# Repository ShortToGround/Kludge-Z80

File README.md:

# Kludge-Z80

A custom and completely kludged together Z80 project.

Table of Contents:
- [Kludge-Z80](#kludge-z80)
  - [About](#about)
  - [Backplane](#backplane)
  - [Card List](#card-list)
    - [Compact Flash Card](#compact-flash-card)
    - [IDE Card](#ide-card)
    - [CPU Card](#cpu-card)
    - [Memory/RAM Card](#memoryram-card)
    - [Network Card](#network-card)
    - [Protoboard Card](#protoboard-card)
    - [PS/2 Card](#ps2-card)
    - [Real-time Clock Card](#real-time-clock-card)
    - [Serial Card](#serial-card)
    - [Sound Card](#sound-card)
    - [Video Card](#video-card)
  - [Bill of Materials](#bill-of-materials)

## About
I've been working on this project off and on since 2017 or, though it was mostly off until recently!
I've designed all of the hardware from scratch, though I'm totally new to this and have no idea what I'm doing.
That's why the project is called Kludge :)

## Backplane
The backplane is a 12-slot board with a full breakout of the Z80 bus. It also has a few spare pins on the bus for future use as well.

I wanted this backplane to be "motherboard-like". At first I was even going to put the CPU and ROM directly on the board! But to make it "motherboard-like" I designed it with status lights (with a breakout too in case I ever put this in a case and want case lights), the reset button on-board, and address decoding on-board as well.

I have designed it to support 5V at 2A load (actually has 3A rated power components!) with a big chunky sliding power switch. This should allow the use of hard disks in the future if they are 5V-only.

NOTE: Because my backplane board length is so long AND the system clock is supplied on the bus directly, I worry about signal reflections. So the backplane features an active termination on-board that holds all of the signals at 2.7V in a push-pull arrangement. 

## Card List
### Compact Flash Card
Compact flash actually has an 8-bit mode built into the spec, which makes interfacing it with vintage 8-bit CPUs pretty easy.

However, in the case of the Z80 the I/O timing differences between the CF and Z80 CPU don't line up perfectly. If you don't account for this in your design you will encounter a decent amount of compact flash cards that will refuse to work, especially newer and faster cards.

The solution is to properly delay the Z80 timings to fit the compact flash true IDE spec.

Someone a lot smarter than me named Tadeusz Pycio came up with a delay circuit to fix this issue.

You can find his blog about it [here](http://www.vtsys.pl/interface-compact-flash/). If you want to read it in English you will need to enter it into google translate though. Google Translate does an excellent job though and its very understandable!

After implementing his circuit into my design I haven't came across a single compact flash card that wouldn't work.

### IDE Card
This is basically the compact flash card circuit but with an 40-pin IDE port instead of compact flash port.

### CPU Card
This is just simply the Z80 CPU broken out onto the bus. There are some pull-ups for the various control signals. It is running off of a 10 MHz oscillator.

I originally designed the RTC circuit to be included but it took up almost all the space on the board and over crowded the CPU and wasn't aesthetically pleasing.

### Memory/RAM Card
This card holds the RAM and EEPROM chips. RAM is bank switched using I/O and also includes the option to totally deactivate the ROM after boot (useful if you are loading a binary on boot from elsewhere).

I adapted some of John's banking and shadow select circuitry into my own.
His documentation and videos have been incredibly useful.

You can visit his awesome Z80 Retro! project [here](https://github.com/Z80-Retro/2063-Z80).

### Network Card
This really should be called "Fast SPI Card" because it's just a parallel
to SPI interface with a header. This circuit was very tricky to build and
I referenced a LOT of other similar builds to piece it together.

### Protoboard Card
A card used to prototype circuits with the Kludge bus.

It's just a 38 x 32 array of 2.54mm spaced pin holes for prototyping.

Why 38 x 32? Because its as much as I could fit in a 100mm x 100mm board to save fab costs :D

### PS/2 Card
This card granted support for both a mouse and keyboard.
It uses a HT6542B to handle all of the PS/2 communication and timing.

### Real-time Clock Card
Like the network card, this is just an SPI circuit as well but the 
RTC IC is embedded on board and this runs a LOT slower than the network card circuit does.

### Serial Card
This card has a single 16550DN UART on-board for serial communication.

### Sound Card
This is a sound card built around the class AY-3-8910.

I am looking to add a second chip in V2 for 3 channel stereo output.

### Video Card
This is centered around an Upduino v3.1 to drive a VGA display. 
The Upduino uses a Lattice iCE40 UP5K UG48 FPGA.
The verilog code for this is available in its own dedicated repo.

## Bill of Materials
The list is pretty large for this whole project. I will compile it and update this later.

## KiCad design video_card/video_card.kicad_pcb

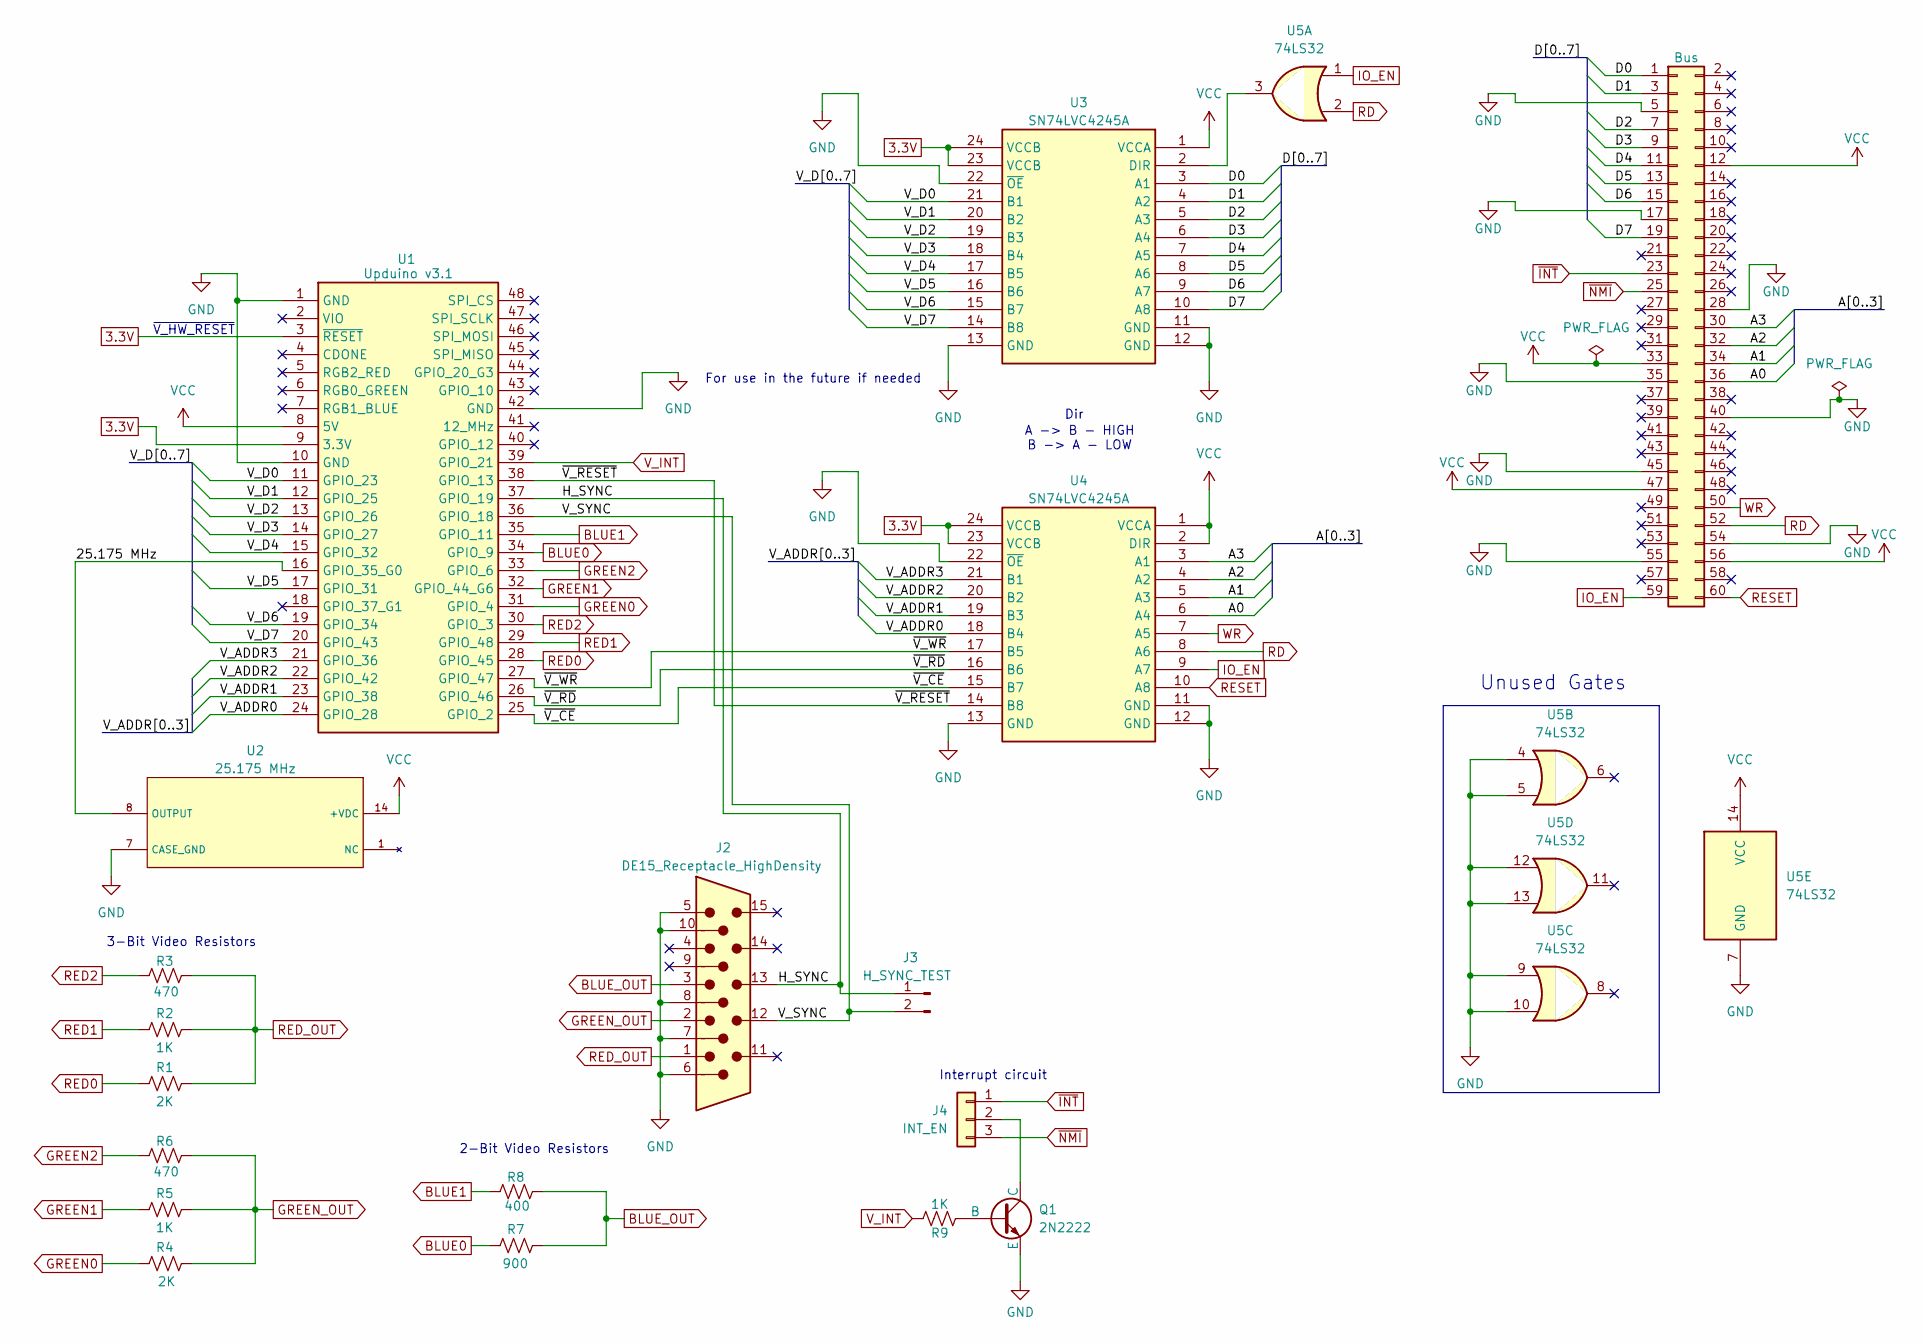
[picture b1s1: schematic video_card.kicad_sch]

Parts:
J1: Bus; PinHeader_2x30_P2.54mm_Vertical
J2: DE15_Receptacle_HighDensity; AMPHENOL_ICD15S13E4GX00LF
J3: H_SYNC_TEST; PinHeader_1x02_P2.54mm_Vertical
J4: INT_EN; PinHeader_1x03_P2.54mm_Vertical
Q1: 2N2222; TO-92
R1, R4: 2K; R_Axial_DIN0207_L6.3mm_D2.5mm_P10.16mm_Horizontal
R2, R5, R9: 1K; R_Axial_DIN0207_L6.3mm_D2.5mm_P10.16mm_Horizontal
R3, R6: 470; R_Axial_DIN0207_L6.3mm_D2.5mm_P10.16mm_Horizontal
R7: 900; R_Axial_DIN0207_L6.3mm_D2.5mm_P10.16mm_Horizontal
R8: 400; R_Axial_DIN0207_L6.3mm_D2.5mm_P10.16mm_Horizontal
U1: Upduino v3.1; UPDUINO V3.1
U2: 25.175 MHz; OSC_ECS-100AX-018
U3, U4: SN74LVC4245A; SN74LVC4245ADWR
U5: 74LS32; DIP-14_W7.62mm_Socket

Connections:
3.3V: U1.3 (~RESET), U1.9 (3.3V), U3.23 (VCCB), U3.24 (VCCB), U4.23 (VCCB), U4.24 (VCCB)
/25.175 MHz: U1.16 (GPIO_35_G0), U2.8 (OUTPUT)
/A0: J1.36, U4.6 (A4)
/A1: J1.34, U4.5 (A3)
/A2: J1.32, U4.4 (A2)
/A3: J1.30, U4.3 (A1)
/D0: J1.1, U3.3 (A1)
/D1: J1.3, U3.4 (A2)
/D2: J1.7, U3.5 (A3)
/D3: J1.9, U3.6 (A4)
/D4: J1.11, U3.7 (A5)
/D5: J1.13, U3.8 (A6)
/D6: J1.15, U3.9 (A7)
/D7: J1.19, U3.10 (A8)
/H_SYNC: J2.13, J3.1, U1.37 (GPIO_19)
/V_ADDR0: U1.24 (GPIO_28), U4.18 (B4)
/V_ADDR1: U1.23 (GPIO_38), U4.19 (B3)
/V_ADDR2: U1.22 (GPIO_42), U4.20 (B2)
/V_ADDR3: U1.21 (GPIO_36), U4.21 (B1)
/V_D0: U1.11 (GPIO_23), U3.21 (B1)
/V_D1: U1.12 (GPIO_25), U3.20 (B2)
/V_D2: U1.13 (GPIO_26), U3.19 (B3)
/V_D3: U1.14 (GPIO_27), U3.18 (B4)
/V_D4: U1.15 (GPIO_32), U3.17 (B5)
/V_D5: U1.17 (GPIO_31), U3.16 (B6)
/V_D6: U1.19 (GPIO_34), U3.15 (B7)
/V_D7: U1.20 (GPIO_43), U3.14 (B8)
/V_SYNC: J2.12, J3.2, U1.36 (GPIO_18)
/~V_CE: U1.25 (GPIO_2), U4.15 (B7)
/~V_RD: U1.26 (GPIO_46), U4.16 (B6)
/~V_RESET: U1.38 (GPIO_13), U4.14 (B8)
/~V_WR: U1.27 (GPIO_47), U4.17 (B5)
BLUE0: R7.1, U1.34 (GPIO_9)
BLUE1: R8.1, U1.35 (GPIO_11)
BLUE_OUT: J2.3, R7.2, R8.2
GND: J1.5, J1.17, J1.28, J1.35, J1.40, J1.45, J1.54, J1.55, J2.5, J2.6, J2.7, J2.8, J2.10, Q1.3 (E), U1.1 (GND), U1.10 (GND), U1.42 (GND), U2.7 (CASE_GND), U3.11 (GND), U3.12 (GND), U3.13 (GND), U3.22 (~OE), U4.11 (GND), U4.12 (GND), U4.13 (GND), U4.22 (~OE), U5.4, U5.5, U5.7 (GND), U5.9, U5.10, U5.12, U5.13
GREEN0: R4.1, U1.31 (GPIO_4)
GREEN1: R5.1, U1.32 (GPIO_44_G6)
GREEN2: R6.1, U1.33 (GPIO_6)
GREEN_OUT: J2.2, R4.2, R5.2, R6.2
IO_EN: J1.59, U4.9 (A7), U5.1
unnamed: J4.2, Q1.1 (C)
unnamed: Q1.2 (B), R9.1
unnamed: U3.2 (DIR), U5.3
RD: J1.52, U4.8 (A6), U5.2
RED0: R1.1, U1.28 (GPIO_45)
RED1: R2.1, U1.29 (GPIO_48)
RED2: R3.1, U1.30 (GPIO_3)
RED_OUT: J2.1, R1.2, R2.2, R3.2
RESET: J1.60, U4.10 (A8)
VCC: J1.12, J1.33, J1.47, J1.56, U1.8 (5V), U2.14 (+VDC), U3.1 (VCCA), U4.1 (VCCA), U4.2 (DIR), U5.14 (VCC)
V_INT: R9.2, U1.39 (GPIO_21)
WR: J1.50, U4.7 (A5)
~INT: J1.23, J4.1
~NMI: J1.25, J4.3

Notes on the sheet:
Unused Gates
A -> B - HIGH B -> A - LOW
Dir
2-Bit Video Resistors
~{V_HW_RESET}
Interrupt circuit
3-Bit Video Resistors
For use in the future if needed

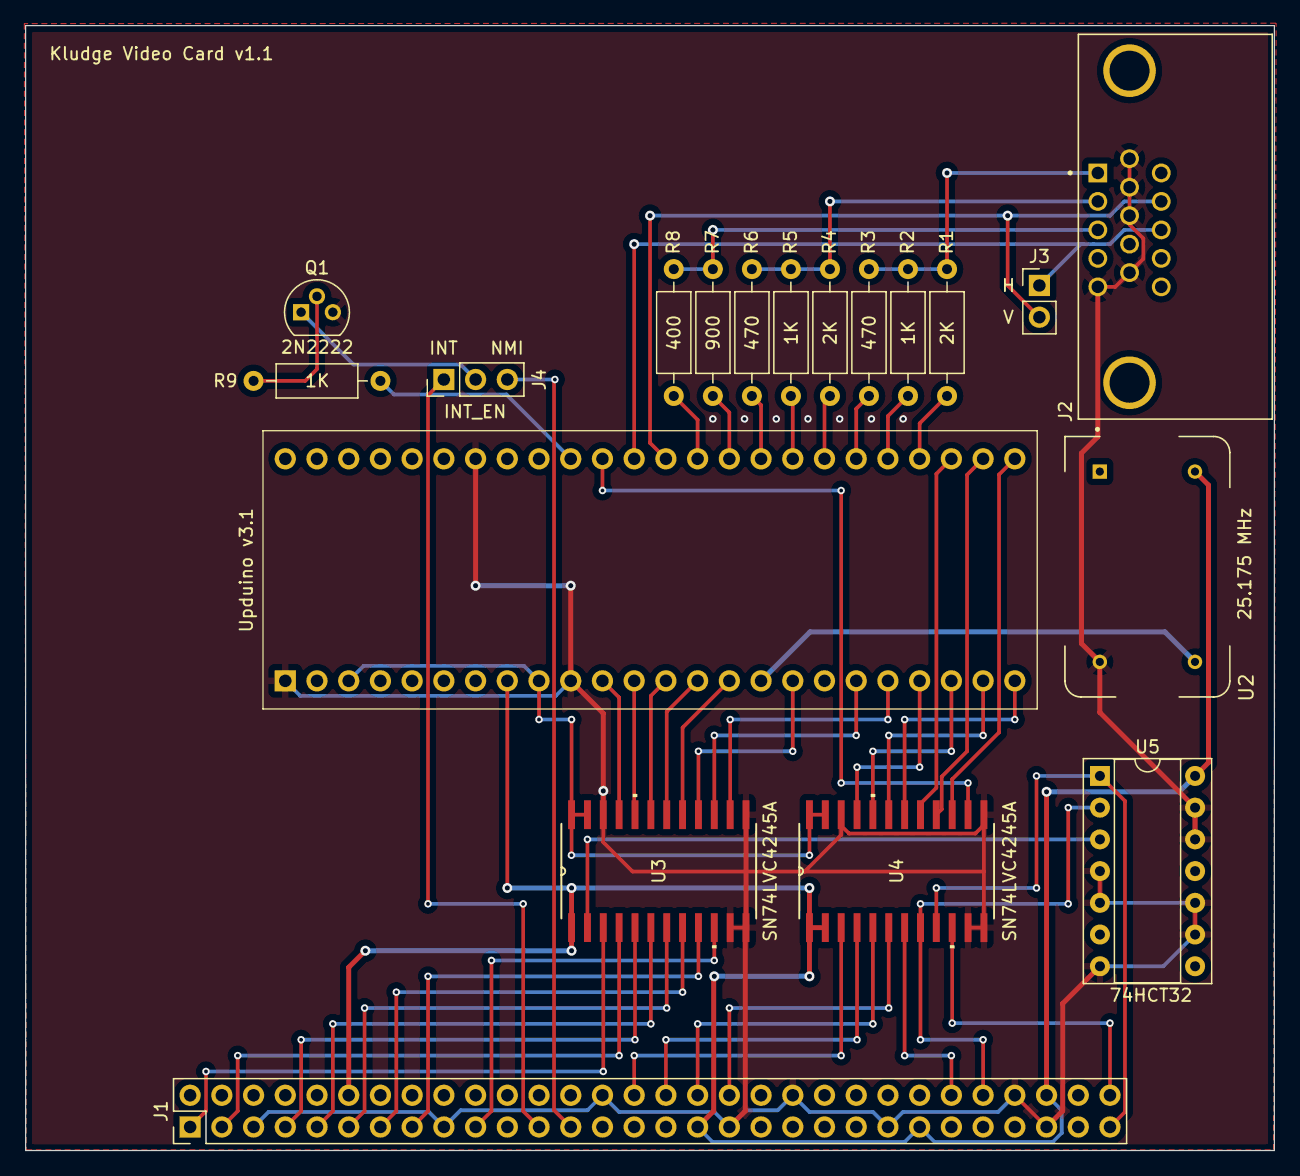
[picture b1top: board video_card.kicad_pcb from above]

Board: 2 copper layers, 100.0 x 90.1 mm, 19 parts (0 on the bottom side), 55 nets.

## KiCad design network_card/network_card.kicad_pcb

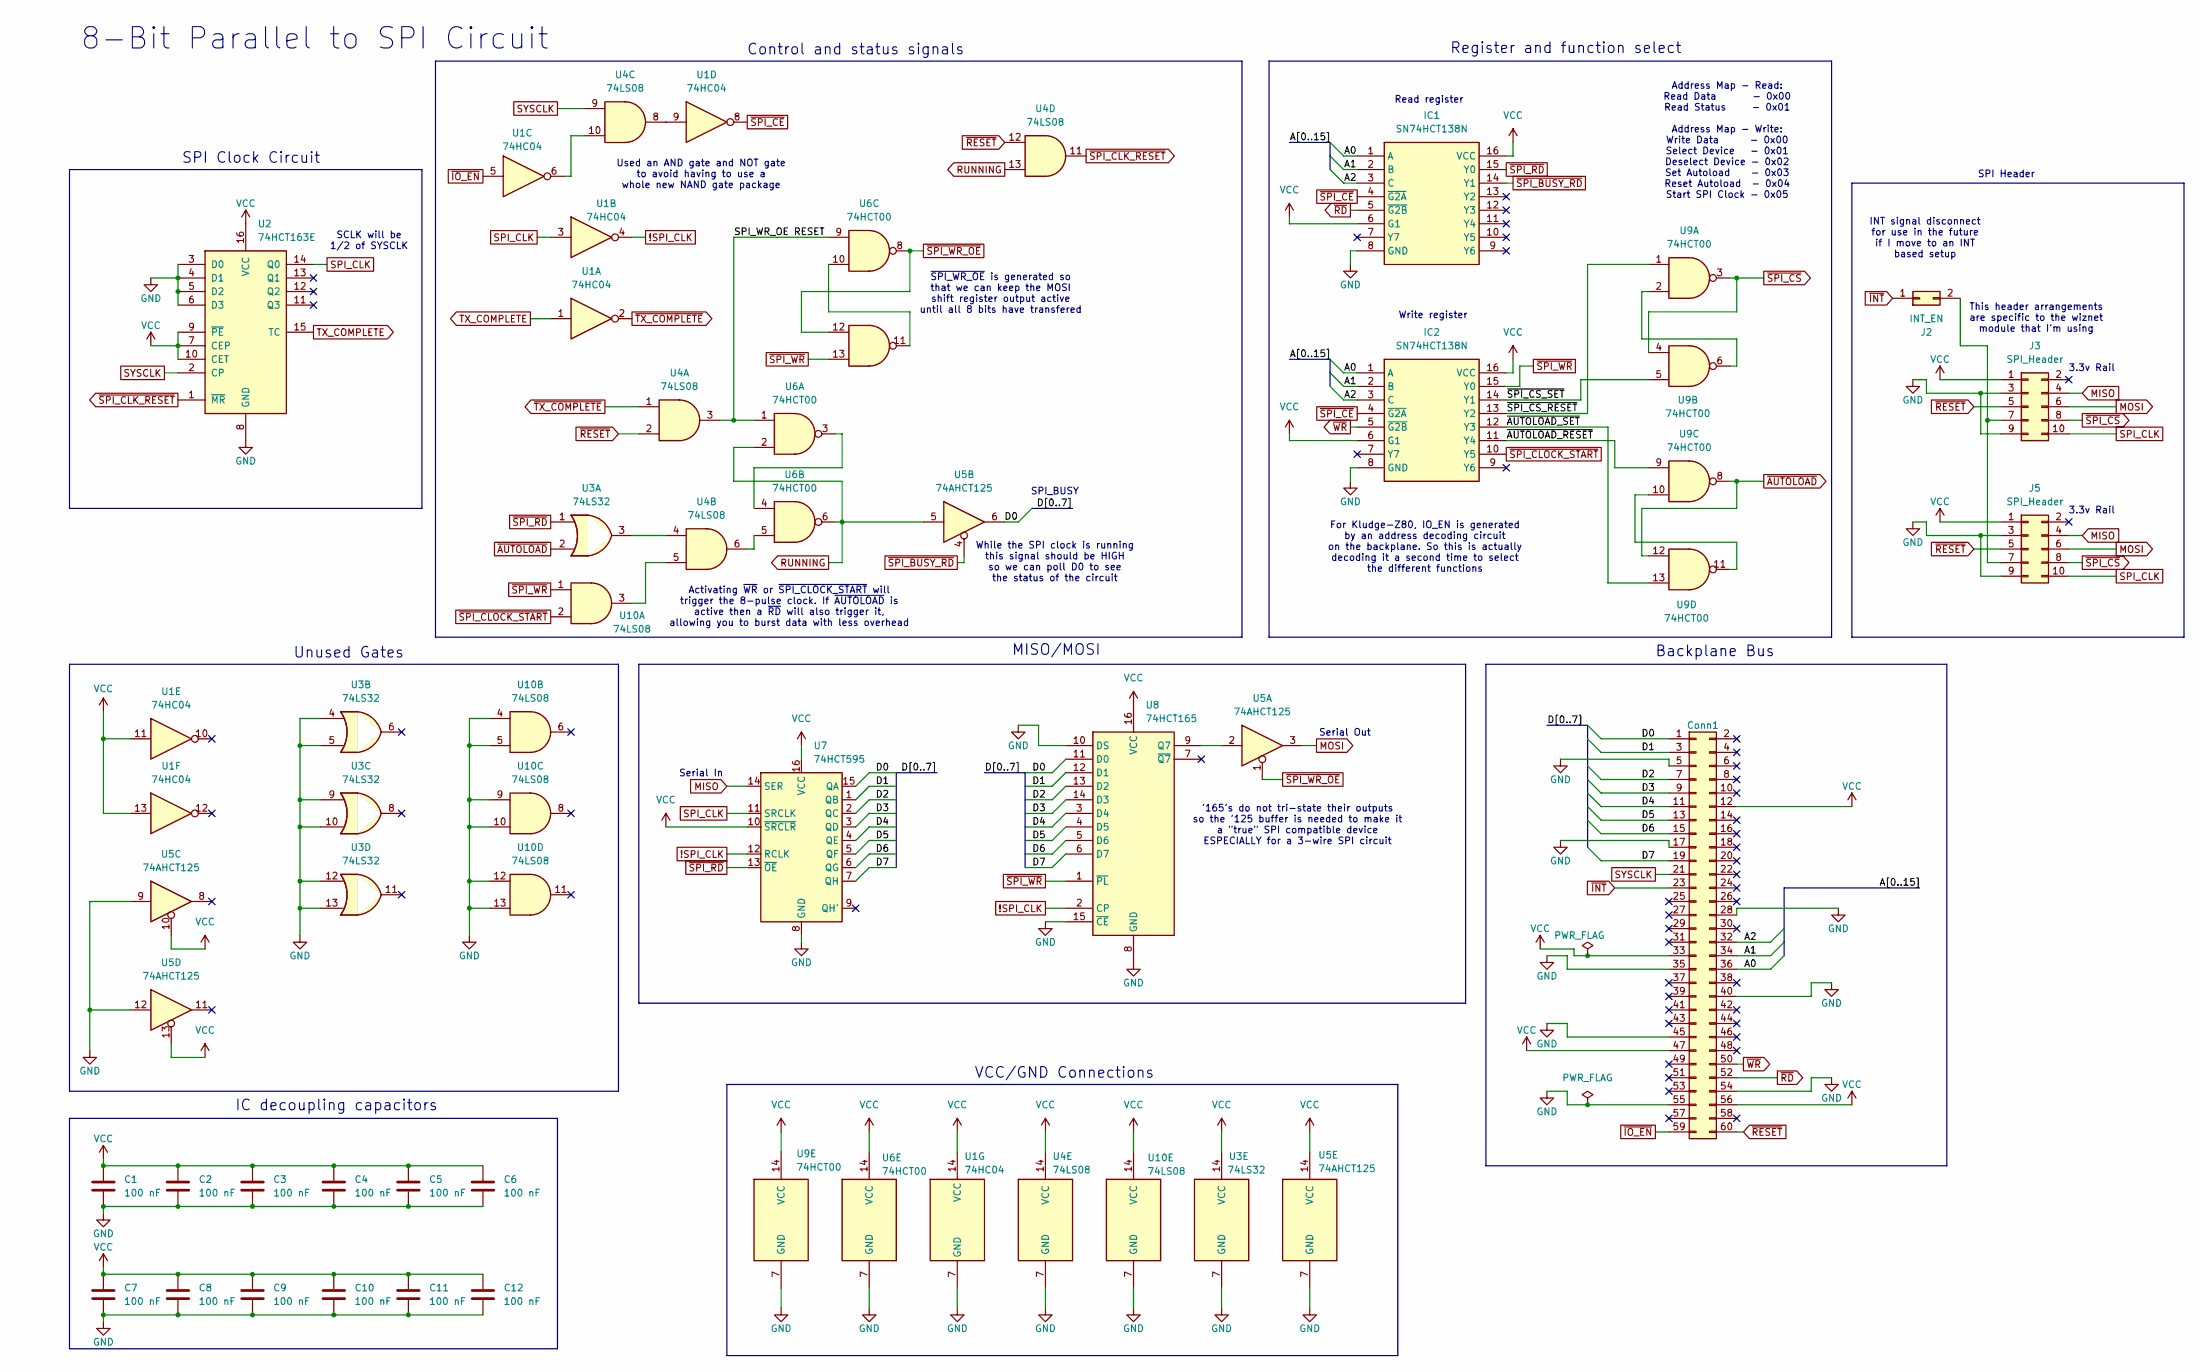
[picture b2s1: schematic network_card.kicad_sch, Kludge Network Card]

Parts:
C1, C2, C3, C4, C5, C6, C7, C8, C9, C10, C11, C12: 100 nF; C_Disc_D3.0mm_W1.6mm_P2.50mm
IC1, IC2: SN74HCT138N; DIP-16_W7.62mm_Socket; Mouser Part Number 595-SN74HCT138N
J1: Conn1; PinHeader_2x30_P2.54mm_Vertical
J2: INT_EN; PinHeader_2x01_P2.54mm_Vertical
J3: SPI_Header; PinHeader_2x05_P2.54mm_Vertical
J5: SPI_Header; IDC-Header_2x05_P2.54mm_Vertical
U1: 74HC04; DIP-14_W7.62mm_Socket
U2: 74HCT163E; DIP-16_W7.62mm_Socket
U3: 74LS32; DIP-14_W7.62mm_Socket
U4, U10: 74LS08; DIP-14_W7.62mm_Socket
U5: 74AHCT125; DIP-14_W7.62mm_Socket
U6, U9: 74HCT00; DIP-14_W7.62mm_Socket
U7: 74HCT595; DIP-16_W7.62mm_Socket
U8: 74HCT165; DIP-16_W7.62mm_Socket

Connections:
!SPI_CLK: U1.4, U7.12 (RCLK), U8.2 (CP)
/A0: IC1.1 (A), IC2.1 (A), J1.36
/A1: IC1.2 (B), IC2.2 (B), J1.34
/A2: IC1.3 (C), IC2.3 (C), J1.32
/D0: J1.1, U5.6, U7.15 (QA), U8.11 (D0)
/D1: J1.3, U7.1 (QB), U8.12 (D1)
/D2: J1.7, U7.2 (QC), U8.13 (D2)
/D3: J1.9, U7.3 (QD), U8.14 (D3)
/D4: J1.11, U7.4 (QE), U8.3 (D4)
/D5: J1.13, U7.5 (QF), U8.4 (D5)
/D6: J1.15, U7.6 (QG), U8.5 (D6)
/D7: J1.19, U7.7 (QH), U8.6 (D7)
/SPI_WR_OE RESET: U4.3, U6.1, U6.9
/~AUTOLOAD_RESET: IC2.11 (Y4), U9.9
/~AUTOLOAD_SET: IC2.12 (Y3), U9.13
/~SPI_CS_RESET: IC2.13 (Y2), U9.1
/~SPI_CS_SET: IC2.14 (Y1), U9.5
GND: C1.2, C2.2, C3.2, C4.2, C5.2, C6.2, C7.2, C8.2, C9.2, C10.2, C11.2, C12.2, IC1.8 (GND), IC2.8 (GND), J1.5, J1.17, J1.28, J1.35, J1.40, J1.45, J1.54, J1.55, J3.3, J3.9, J5.3, J5.9, U1.7 (GND), U2.3 (D0), U2.4 (D1), U2.5 (D2), U2.6 (D3), U2.8 (GND), U3.4, U3.5, U3.7 (GND), U3.9, U3.10, U3.12, U3.13, U4.7 (GND), U5.7 (GND), U5.9, U5.12, U6.7 (GND), U7.8 (GND), U8.8 (GND), U8.10 (DS), U8.15 (~CE), U9.7 (GND), U10.4, U10.5, U10.7 (GND), U10.9, U10.10, U10.12, U10.13
MISO: J3.4, J5.4, U7.14 (SER)
MOSI: J3.6, J5.6, U5.3
unnamed: J2.2, J3.7, J5.7
unnamed: U1.6, U4.10
unnamed: U1.9, U4.8
unnamed: U3.3, U4.4
unnamed: U4.6, U6.5
unnamed: U6.3, U6.4
unnamed: U6.10, U6.11
unnamed: U5.2, U8.9 (Q7)
unnamed: U9.2, U9.6
unnamed: U9.10, U9.11
unnamed: U4.5, U10.3
RUNNING: U4.13, U5.5, U6.2, U6.6
SPI_CLK: J3.10, J5.10, U1.3, U2.14 (Q0), U7.11 (SRCLK)
SYSCLK: J1.21, U2.2 (CP), U4.9
TX_COMPLETE: U1.1, U2.15 (TC)
VCC: C1.1, C2.1, C3.1, C4.1, C5.1, C6.1, C7.1, C8.1, C9.1, C10.1, C11.1, C12.1, IC1.6 (G1), IC1.16 (VCC), IC2.6 (G1), IC2.16 (VCC), J1.12, J1.33, J1.47, J1.56, J3.1, J5.1, U1.11, U1.13, U1.14 (VCC), U2.7 (CEP), U2.9 (~PE), U2.10 (CET), U2.16 (VCC), U3.14 (VCC), U4.14 (VCC), U5.10, U5.13, U5.14 (VCC), U6.14 (VCC), U7.10 (~SRCLR), U7.16 (VCC), U8.16 (VCC), U9.14 (VCC), U10.14 (VCC)
~AUTOLOAD: U3.2, U9.8, U9.12
~INT: J1.23, J2.1
~IO_EN: J1.59, U1.5
~RD: IC1.5 (~G2B), J1.52
~RESET: J1.60, J3.5, J5.5, U4.2, U4.12
~SPI_BUSY_RD: IC1.14 (Y1), U5.4
~SPI_CE: IC1.4 (~G2A), IC2.4 (~G2A), U1.8
~SPI_CLK_RESET: U2.1 (~MR), U4.11
~SPI_CLOCK_START: IC2.10 (Y5), U10.2
~SPI_CS: J3.8, J5.8, U9.3, U9.4
~SPI_RD: IC1.15 (Y0), U3.1, U7.13 (~OE)
~SPI_WR_OE: U5.1, U6.8, U6.12
~SPI_WR: IC2.15 (Y0), U6.13, U8.1 (~PL), U10.1
~TX_COMPLETE: U1.2, U4.1
~WR: IC2.5 (~G2B), J1.50

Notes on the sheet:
Used an AND gate and NOT gate to avoid having to use a whole new NAND gate package
MISO/MOSI
This header arrangements are specific to the wiznet module that I'm using
Control and status signals
Write register
3.3v Rail
Serial In
Serial Out
While the SPI clock is running this signal should be HIGH so we can poll D0 to see the status of the circuit
Address Map - Read: Read Data - 0x00 Read Status - 0x01 Address Map - Write: Write Data - 0x00 Select Device - 0x01 Deselect Device - 0x02 Set Autoload - 0x03 Reset Autoload - 0x04 Start SPI Clock - 0x05
SPI Header
IC decoupling capacitors
Unused Gates
For Kludge-Z80, IO_EN is generated by an address decoding circuit on the backplane. So this is actually decoding it a second time to select the different functions
Activating ~{WR} or ~{SPI_CLOCK_START} will trigger the 8-pulse clock. If ~{AUTOLOAD} is active then a ~{RD} will also trigger it, allowing you to burst data with less overhead
8-Bit Parallel to SPI Circuit
Register and function select
~{SPI_WR_OE} is generated so that we can keep the MOSI shift register output active until all 8 bits have transfered
Backplane Bus
VCC/GND Connections
SCLK will be 1/2 of SYSCLK
SPI_BUSY
Read register
INT signal disconnect for use in the future if I move to an INT based setup
SPI Clock Circuit
'165's do not tri-state their outputs so the '125 buffer is needed to make it a "true" SPI compatible device ESPECIALLY for a 3-wire SPI circuit

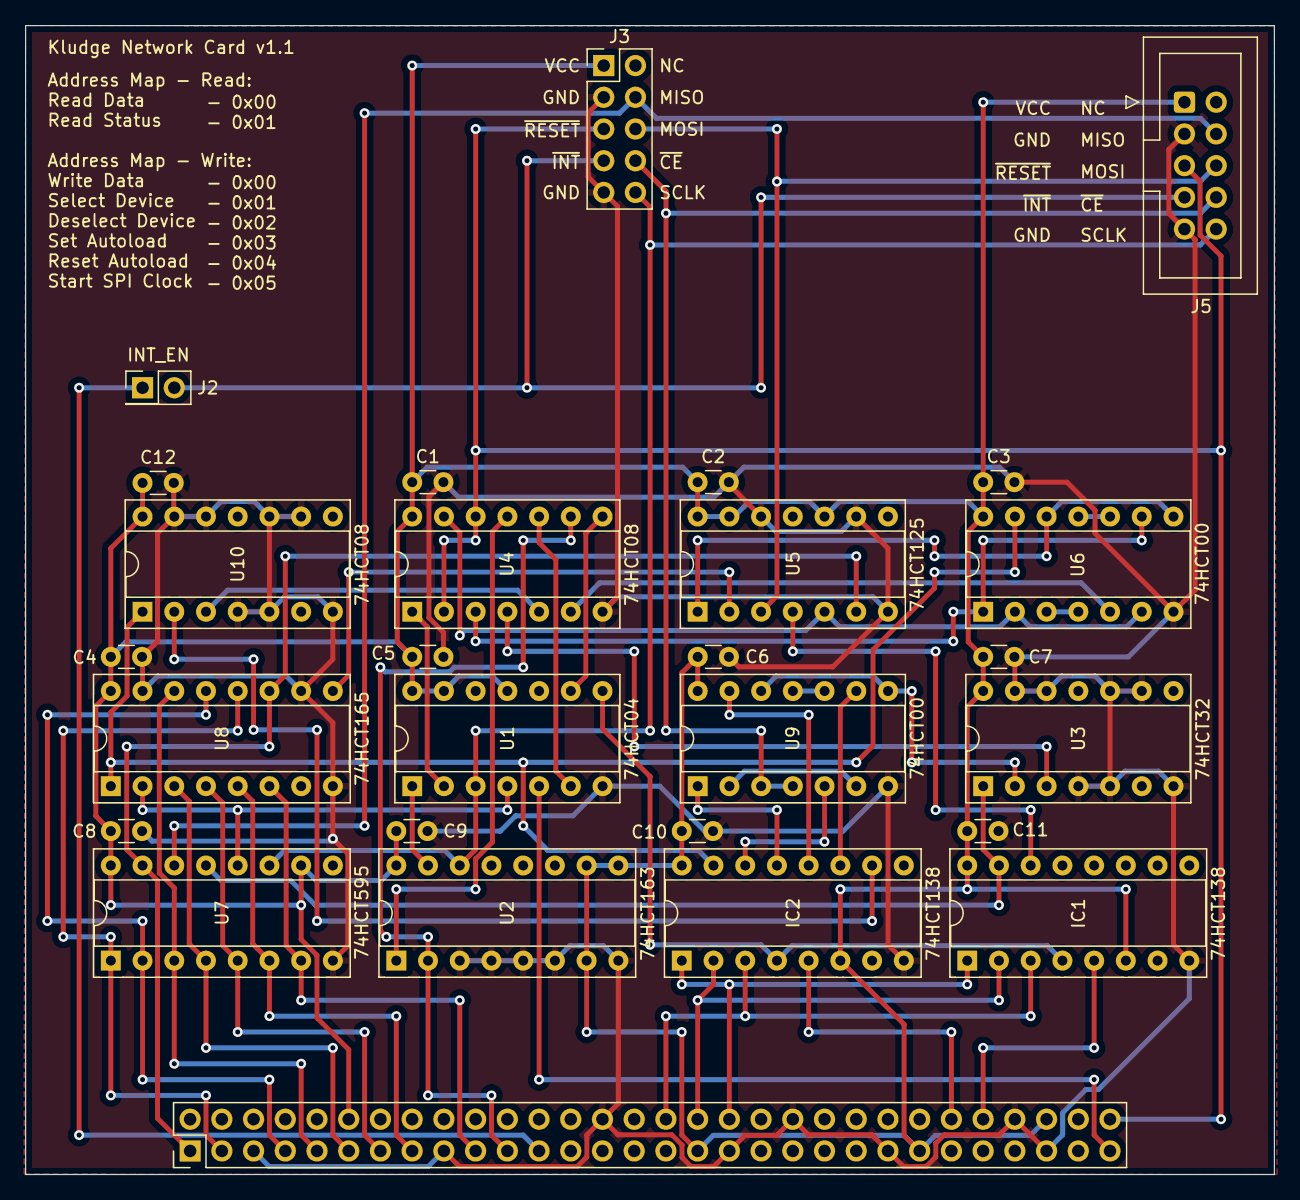
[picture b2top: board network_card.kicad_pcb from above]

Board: 2 copper layers, 100.0 x 92.0 mm, 28 parts (0 on the bottom side), 51 nets.

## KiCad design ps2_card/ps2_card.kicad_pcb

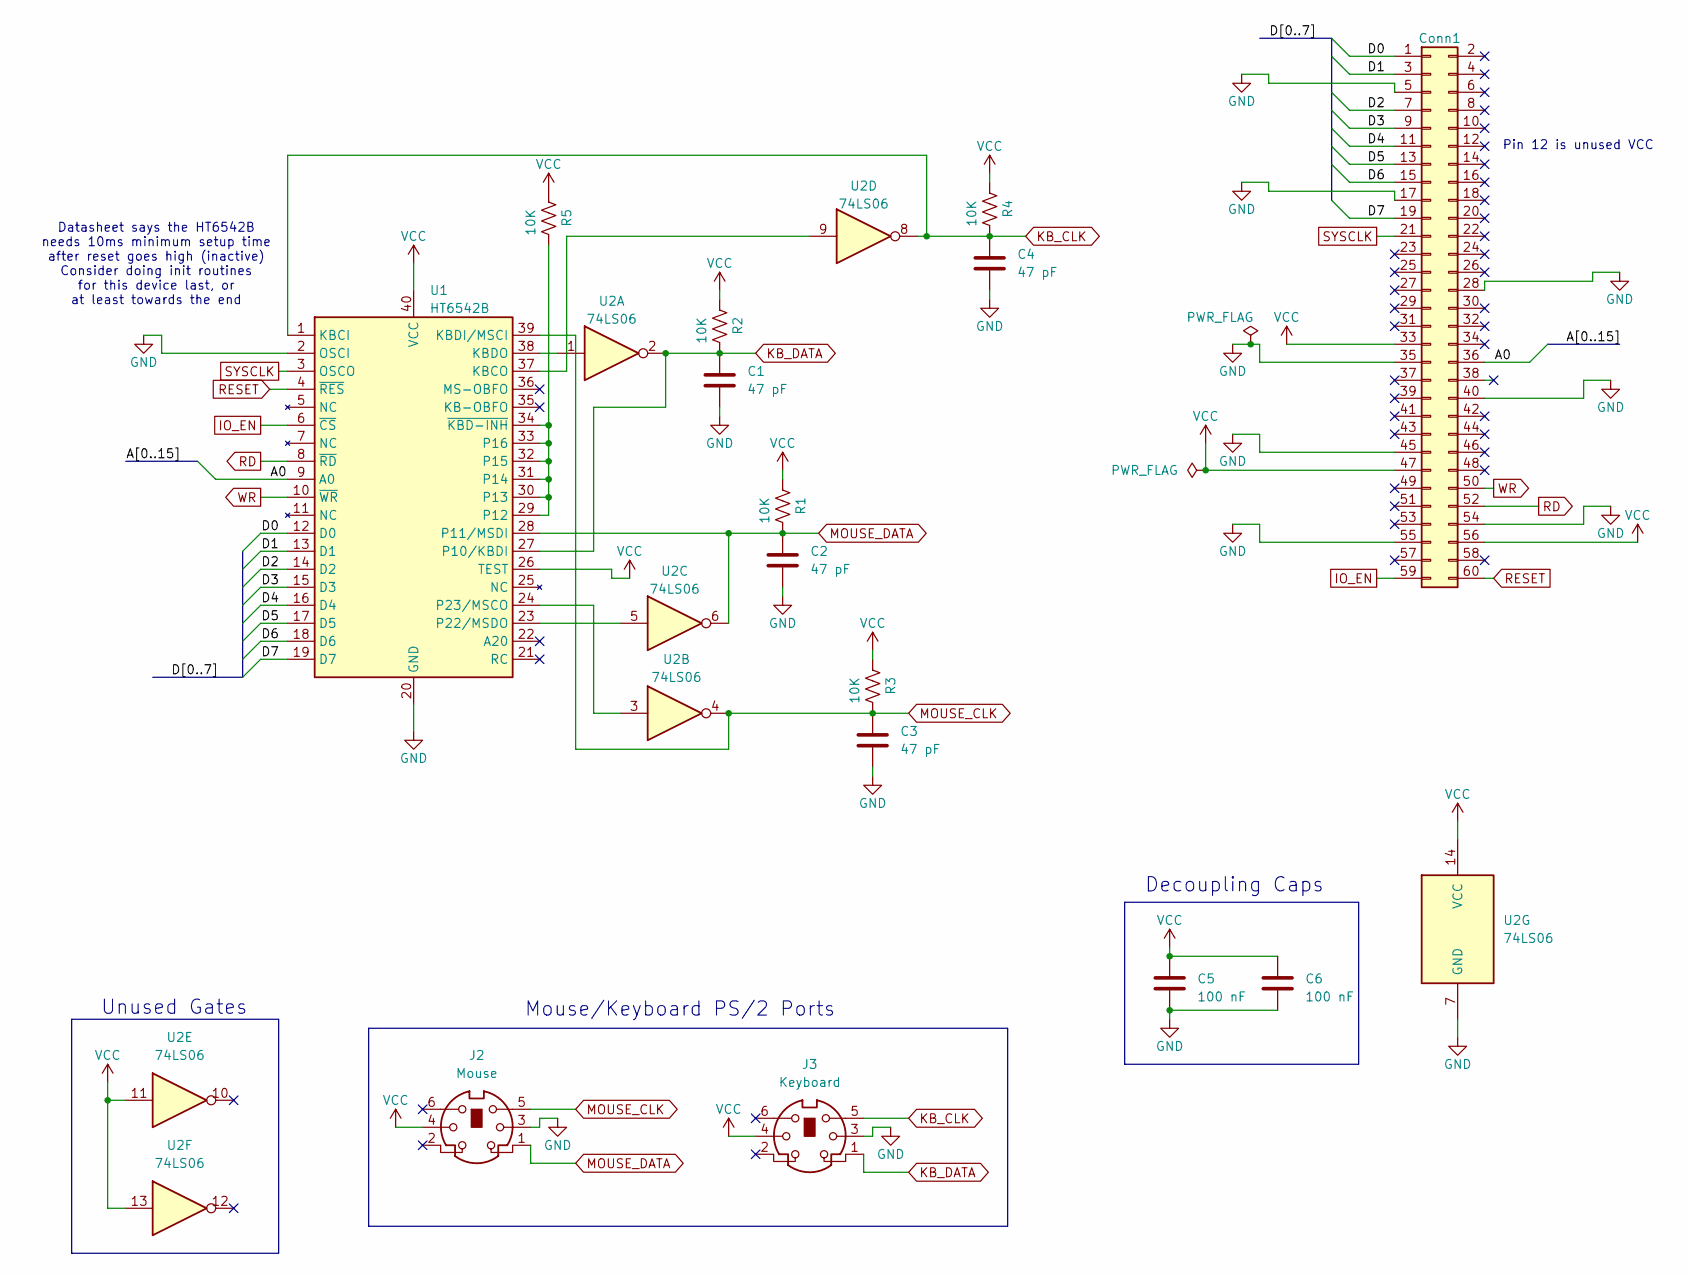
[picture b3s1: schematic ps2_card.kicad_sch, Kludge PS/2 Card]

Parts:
C1, C2, C3, C4: 47 pF; C_Disc_D3.0mm_W1.6mm_P2.50mm
C5, C6: 100 nF; C_Disc_D3.0mm_W1.6mm_P2.50mm
J1: Conn1; PinHeader_2x30_P2.54mm_Vertical
J2: Mouse; CONN_5749180-1_TYC
J3: Keyboard; CONN_5749180-1_TYC
R1, R2, R3, R4, R5: 10K; R_Axial_DIN0207_L6.3mm_D2.5mm_P10.16mm_Horizontal
U1: HT6542B; DIP-40_W15.24mm
U2: 74LS06; DIP-14_W7.62mm

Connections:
/A0: J1.36, U1.9 (A0)
/D0: J1.1, U1.12 (D0)
/D1: J1.3, U1.13 (D1)
/D2: J1.7, U1.14 (D2)
/D3: J1.9, U1.15 (D3)
/D4: J1.11, U1.16 (D4)
/D5: J1.13, U1.17 (D5)
/D6: J1.15, U1.18 (D6)
/D7: J1.19, U1.19 (D7)
GND: C1.2, C2.2, C3.2, C4.2, C5.2, C6.2, J1.5, J1.17, J1.28, J1.35, J1.40, J1.45, J1.54, J1.55, J2.3, J3.3, U1.2 (OSCI), U1.20 (GND), U2.7 (GND)
IO_EN: J1.59, U1.6 (~CS)
KB_CLK: C4.1, J3.5, R4.2, U1.1 (KBCI), U2.8
KB_DATA: C1.1, J3.1, R2.2, U1.27 (P10/KBDI), U2.2
MOUSE_CLK: C3.1, J2.5, R3.2, U1.39 (KBDI/MSCI), U2.4
MOUSE_DATA: C2.1, J2.1, R1.2, U1.28 (P11/MSDI), U2.6
unnamed: U1.37 (KBCO), U2.9
unnamed: U1.38 (KBDO), U2.1
unnamed: R5.2, U1.29 (P12), U1.30 (P13), U1.31 (P14), U1.32 (P15), U1.33 (P16), U1.34 (~KBD-INH)
unnamed: U1.23 (P22/MSDO), U2.5
unnamed: U1.24 (P23/MSCO), U2.3
RD: J1.52, U1.8 (~RD)
RESET: J1.60, U1.4 (~RES)
SYSCLK: J1.21, U1.3 (OSCO)
VCC: C5.1, C6.1, J1.33, J1.47, J1.56, J2.4, J3.4, R1.1, R2.1, R3.1, R4.1, R5.1, U1.26 (TEST), U1.40 (VCC), U2.11, U2.13, U2.14 (VCC)
WR: J1.50, U1.10 (~WR)

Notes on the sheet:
Datasheet says the HT6542B needs 10ms minimum setup time after reset goes high (inactive) Consider doing init routines for this device last, or at least towards the end
Unused Gates
Pin 12 is unused VCC
Mouse/Keyboard PS/2 Ports
Decoupling Caps

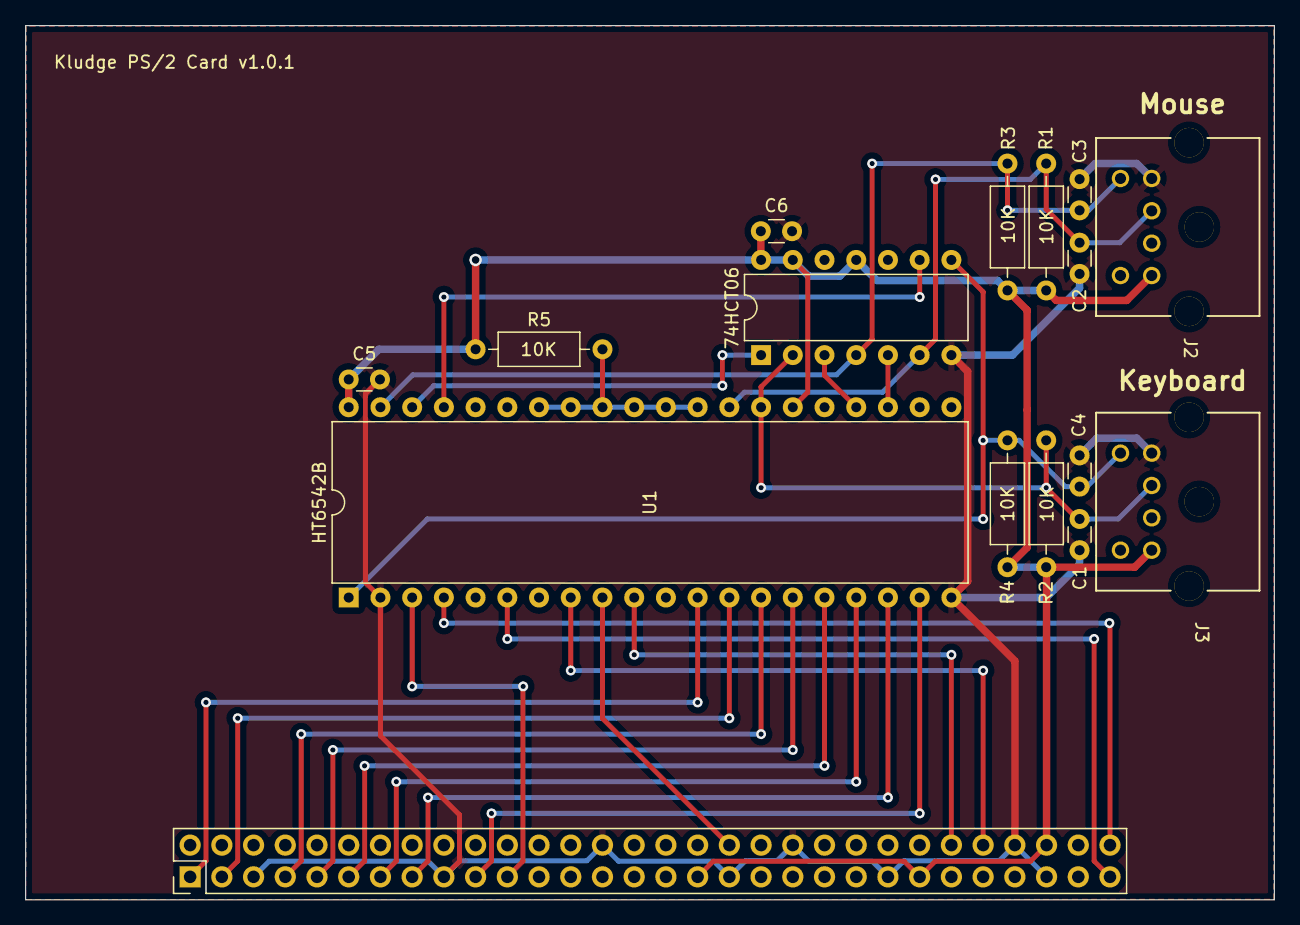
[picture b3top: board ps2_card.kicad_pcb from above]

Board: 2 copper layers, 100.0 x 70.0 mm, 16 parts (0 on the bottom side), 25 nets.
